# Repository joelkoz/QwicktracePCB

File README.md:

# Qwicktrace Pro PCB
Qwicktrace PCB is the software component of the QwickFab PCB open source desktop circuit board fabrication system.
The system dramatically reduces the time and skill required to make top quality single and double sided circuit 
boards for prototyping and one off use. Using QwickFab PCB, making a PCB is as simple as uploading your Gerber files to 
the Pro controller, selecting the process you wish to use to create the board, and then following the on-screen step
by step instructions. 

# Overview
The QwickFab desktop fabrication system consists of three major hardware components and one optional one:

1. The Qwicktrace Pro Controller is small control device with touchscreen and joystick powered by a Raspberry Pi 4 and the software
found in this repository. It is comprised of a software stack and UI for controlling the other two hardware components below. The 
Controller can run either of the two other components individually, or together as a complete desktop PCB fabrication system.

2. The Qwicktrace Exposure Table is a small device for quickly exposing photosensitive copper boards to ultraviolet light masked using a process called "Masked Stereolithography" (MSLA). The all new design of this exposure system adds an amber LED "safe light" for illuminating the mask for end user board positioning that is invisible to the photosenstive board.

3. The Qwickmill mini CNC is a small desktop CNC machine designed specifically for working with small printed circuit boards. It can
quickly drill the holes needed by through hole components on boards processed with the Exposure table.  It can also mill an entire PCB on blank copper boards using special ingraving bits. This is handy if your board is simple enough as to not need the better resolution of the exposure table, or if you are on a budget and would prefer not to spend the extra money on photosensitive boards. 
Finally, the Qwickmill can be used to cut board stock down to smaller sizes.

4. The QwickEtch Etching tank is a small container that can be used to quickly etch boards exposed with the Exposure table using
a minimal mount of equipment. While any type of container can be used, the QwickEtch tank has an air pump powered agitator in
in, removing the need for you to manually rock the etching tank.

The software on the Pro Controller (source code found on this repo) handles the more challenging aspects of making a PCB, such as aligning the drilling with the traces made on the exposure table, or positioning the opposite side of a board on a double sided PCB.

While the above hardware components make for a convenient set of tools, many Makers already have existing equipment they'd like
to use in place of a QwickFab component. You are free to mix and match any or all of the components that you wish.  You could
in theory build NONE of the hardware components and simply run the Qwicktrace software on an old laptop or pre-existing 
Raspberry Pi build.  The Qwickmill is built upon the open source standard Grbl controller. If you already own a CNC machines that uses Grbl, you can use that instead. It is easy to create a cable that connects from the Pro Controller to any CNC machine, such a 3018 or 1610. If you are on a budget, you can sometimes source a kit for one of these machines for less money than the individual parts for building the Qwickmill.

# Software features

* Creates PCB trace masks directly from Gerber files in SVG for MSLA exposure and/or in g-code for isolation milling
* Software deskewing of traces and drill holes makes combining MSLA, milling, and/or double sided boards quick and easy.
* Software autoleveling ensures isolation milling traces are cut to perfect depth
* Drill/mill features works with any Grbl compatible CNC controller
* UI designed for small 3.5" touchscreen
* Supports joystick input via ADS1115 for easy jogging of CNC machine and alignment of drill holes
* Turns Raspberry Pi into a remote access server and controller for Grbl CNC machines

# DIY construction of a QwickFab system

The Qwickfab Pro system is made from parts printed with your 3D printer as well as easy to obtain off the shelf parts. The
STL files for this project can be found here in this repo in the `hardware/*/stl` directories. A complete bill of materials can be
found in the `docs` directory.

Build instructions with project discussion is located on the project's [Hackaday Project Page](https://hackaday.io/project/182645-qwickfab-pcb)

To install the software on the Raspberry Pi, see the file `Setting up Raspberry Pi`, also in `docs`

# Development

The Qwicktrace user interface on the Pro Controller is a touchscreen app written in NodeJS/Javascript and built with the
Electron framework.  This UI is layered on top of a software stack comprised of many great open source software packages. These include:

1. [Tracespace](https://github.com/tracespace) Gerber processing library for Javascript
2. [pcb2gcode](https://github.com/pcb2gcode/pcb2gcode) Gerber to GCode utility for milling isolation traces
3. [CNCjs](https://github.com/cncjs/cncjs) Web interface and Grbl server for CNC machine control
4. [EventEmitter2](https://github.com/EventEmitter2/EventEmitter2) Advanced event handling for NodeJS

For additional technical information on the Qwicktrace software architecture, see the `docs` directory

---
### Do you find my work useful?

---

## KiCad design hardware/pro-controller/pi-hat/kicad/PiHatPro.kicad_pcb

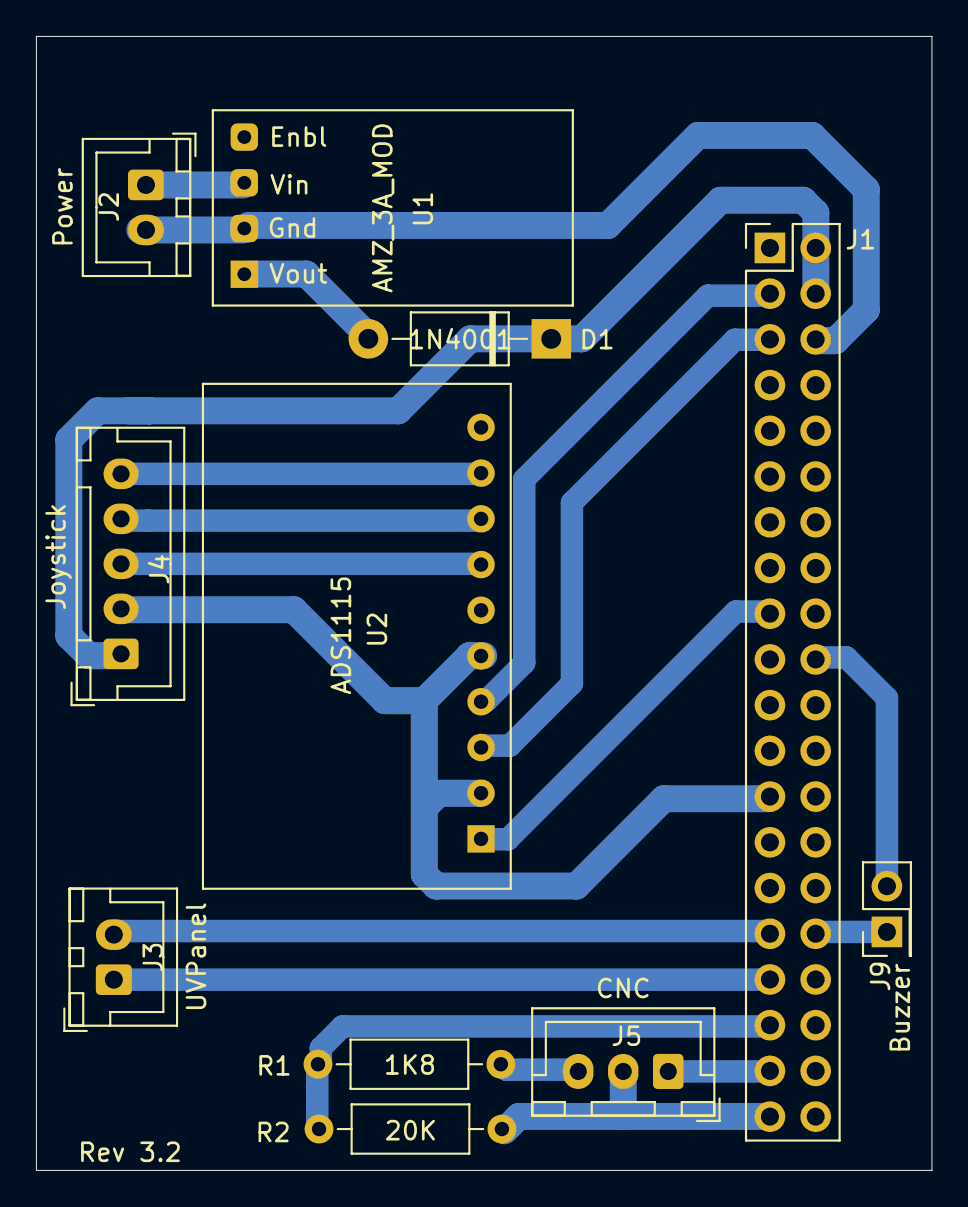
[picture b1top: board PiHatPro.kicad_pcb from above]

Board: 4 copper layers, 49.8 x 63.0 mm, 11 parts (0 on the bottom side), 16 nets.

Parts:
D1: 1N4001; D_DO-41_SOD81_P10.16mm_Horizontal
J1: Raspberry_Pi_2_3; PinSocket_2x20_P2.54mm_BacksideMount
J2: Power; JST_XH_B2B-XH-A_1x02_P2.50mm_Vertical
J3: UVPanel; JST_XH_B2B-XH-A_1x02_P2.50mm_Vertical
J4: Joystick; JST_XH_B5B-XH-A_1x05_P2.50mm_Vertical
J5: CNC; JST_XH_B3B-XH-A_1x03_P2.50mm_Vertical
J9: Buzzer; PinHeader_2x01_P2.54mm_Vertical
R1: 1K8; R_Axial_DIN0207_L6.3mm_D2.5mm_P10.16mm_Horizontal
R2: 20K; R_Axial_DIN0207_L6.3mm_D2.5mm_P10.16mm_Horizontal
U1: AMZ_3A_MOD; Amazon_3A_Power_Module
U2: ADS1115; Adafruit_ADS1115_Module

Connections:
+3V3: J1.1, J1.17, U2.1
+5V: D1.1, J1.2, J1.4, J4.1
+24V: J2.1, U1.3
Buzzer: J1.32, J9.1
GND: J1.6, J1.9, J1.14, J1.20, J1.25, J1.30, J1.34, J1.39, J2.2, J4.2, J5.2, J9.2, R2.2, U1.2, U2.2, U2.5
JOYSTICK_SW: J4.5, U2.9
JOYSTICK_X: J4.3, U2.7
JOYSTICK_Y: J4.4, U2.8
LaserControl: J1.37, J5.1
unnamed: D1.2, U1.1
SCL: J1.5, U2.3
SDA: J1.3, U2.4
UVExpose: J1.31, J3.2
UVSafe: J1.33, J3.1
ZProbe3V3: J1.35, R1.2, R2.1
ZProbeIn: J5.3, R1.1

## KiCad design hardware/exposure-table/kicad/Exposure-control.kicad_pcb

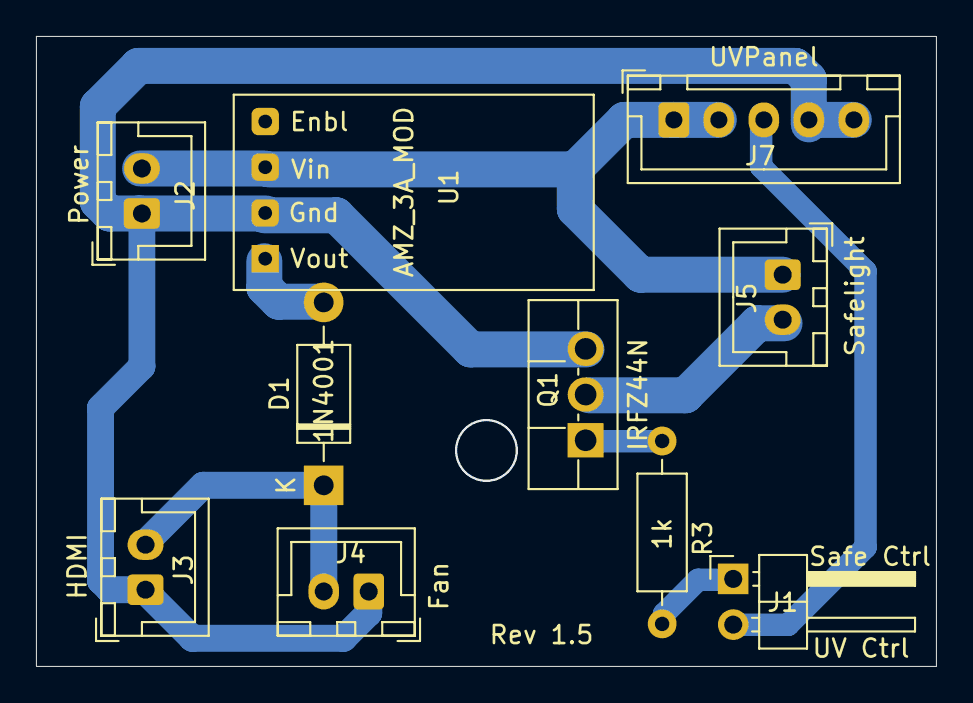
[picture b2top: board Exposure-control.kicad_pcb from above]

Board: 2 copper layers, 50.0 x 35.0 mm, 10 parts (0 on the bottom side), 8 nets.

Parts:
D1: 1N4001; D_DO-41_SOD81_P10.16mm_Horizontal
J1: Light Control; PinHeader_1x02_P2.54mm_Horizontal
J2: Power; JST_XH_B2B-XH-A_1x02_P2.50mm_Vertical
J3: HDMI; JST_XH_B2B-XH-A_1x02_P2.50mm_Vertical
J4: Fan; JST_XH_B2B-XH-A_1x02_P2.50mm_Vertical
J5: Safelight; JST_XH_B2B-XH-A_1x02_P2.50mm_Vertical
J7: UVPanel; JST_XH_B5B-XH-A_1x05_P2.50mm_Vertical
Q1: IRFZ44N; TO-220F-3_Vertical
R3: 1k; R_Axial_DIN0207_L6.3mm_D2.5mm_P10.16mm_Horizontal
U1: AMZ_3A_MOD; Amazon_3A_Power_Module

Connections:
+5V: D1.1, J3.2, J4.2
+24V: J2.2, J5.1, J7.1, J7.2, U1.3
GND: J2.1, J3.1, J4.1, J7.4, J7.5, Q1.3, U1.2
unnamed: D1.2, U1.1
unnamed: Q1.1, R3.2
SafelightControl: J1.1, R3.1
SafelightGnd: J5.2, Q1.2
UVControl: J1.2, J7.3

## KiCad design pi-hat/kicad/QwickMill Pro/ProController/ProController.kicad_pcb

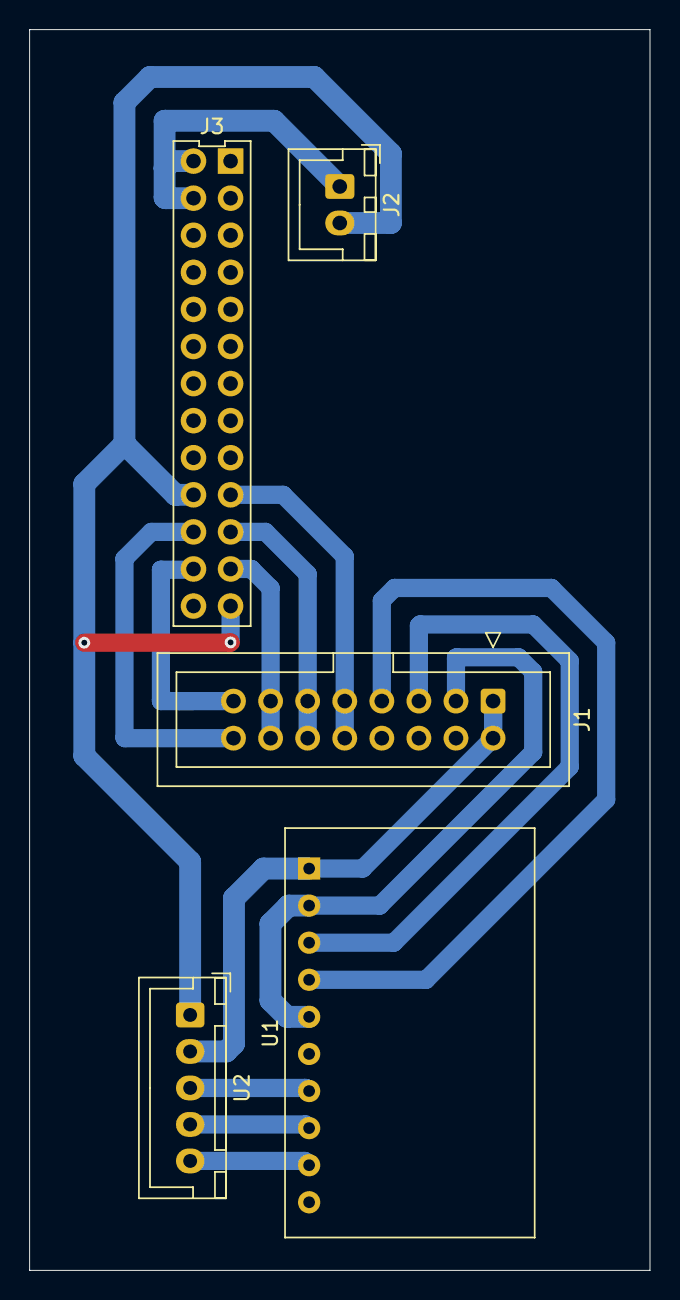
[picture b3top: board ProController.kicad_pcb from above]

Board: 2 copper layers, 42.5 x 85.0 mm, 5 parts (0 on the bottom side), 13 nets.

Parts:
J1: IDC16; IDC-Header_2x08_P2.54mm_Vertical
J2: Pro Power; JST_XH_B2B-XH-A_1x02_P2.50mm_Vertical
J3: HDMI-LCD; Pi_Header_Pins_Backside_Mount_26
U1: ADS1115; Adafruit_ADS1115_Module
U2: JOYSTICK; JST_XH_B5B-XH-A_1x05_P2.50mm_Vertical

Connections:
+3V3: J1.1, J1.2, U1.1, U2.2
+5V: J2.1, J3.2, J3.4
GND: J1.3, J2.2, J3.20, J3.25, U1.2, U1.5, U2.1
MISO: J1.11, J1.12, J3.21
MOSI: J1.9, J1.10, J3.19
SCL: J1.5, U1.3
SDA: J1.7, U1.4
SLCK: J1.13, J1.14, J3.23
SW: U1.9, U2.5
T_CS: J1.15, J3.24
T_IRQ: J1.16, J3.22
VRX: U1.7, U2.3
VRY: U1.8, U2.4

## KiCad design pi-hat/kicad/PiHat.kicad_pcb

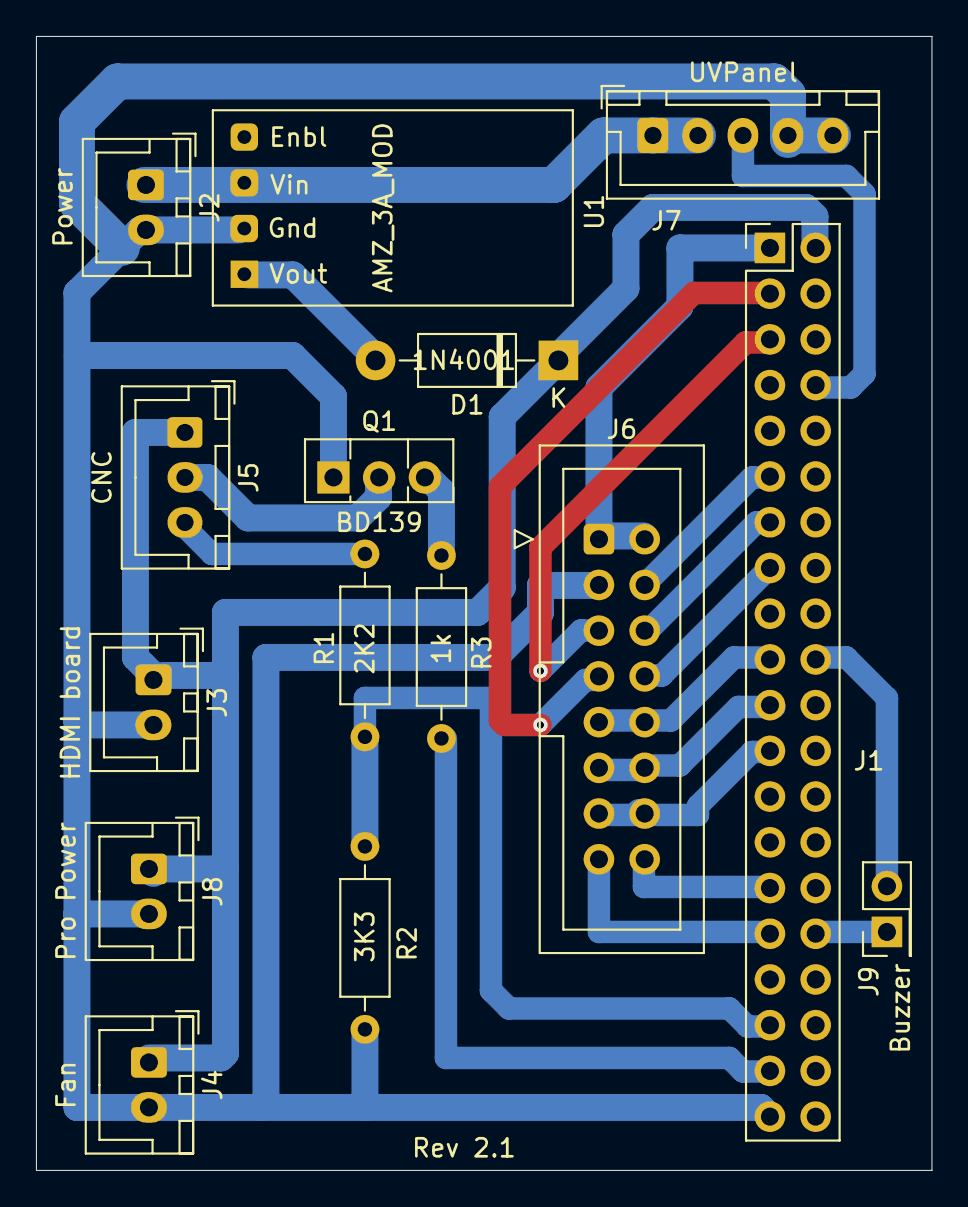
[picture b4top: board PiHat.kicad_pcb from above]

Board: 2 copper layers, 49.8 x 63.0 mm, 15 parts (0 on the bottom side), 22 nets.

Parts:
D1: 1N4001; D_DO-41_SOD81_P10.16mm_Horizontal
J1: Raspberry_Pi_2_3; PinSocket_2x20_P2.54mm_BacksideMount
J2: Power; JST_XH_B2B-XH-A_1x02_P2.50mm_Vertical
J3: HDMI board; JST_XH_B2B-XH-A_1x02_P2.50mm_Vertical
J4: Fan; JST_XH_B2B-XH-A_1x02_P2.50mm_Vertical
J5: CNC; JST_XH_B3B-XH-A_1x03_P2.50mm_Vertical
J6: IDC16; IDC-Header_2x08_P2.54mm_Vertical
J7: UVPanel; JST_XH_B5B-XH-A_1x05_P2.50mm_Vertical
J8: Pro Power; JST_XH_B2B-XH-A_1x02_P2.50mm_Vertical
J9: Buzzer; PinHeader_2x01_P2.54mm_Vertical
Q1: BD139; TO-126-3_Vertical
R1: 2K2; R_Axial_DIN0207_L6.3mm_D2.5mm_P10.16mm_Horizontal
R2: 3K3; R_Axial_DIN0207_L6.3mm_D2.5mm_P10.16mm_Horizontal
R3: 1k; R_Axial_DIN0207_L6.3mm_D2.5mm_P10.16mm_Horizontal
U1: AMZ_3A_MOD; Amazon_3A_Power_Module

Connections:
+3V3: J1.1, J6.1, J6.2
+5V: D1.1, J1.2, J3.1, J4.1, J5.1, J8.1
+24V: J2.1, J7.1, J7.2, U1.3
Buzzer: J1.32, J9.1
CS: J1.11, J6.4
DC: J1.13, J6.6
GND: J1.20, J1.39, J2.2, J3.2, J4.2, J6.3, J7.4, J7.5, J8.2, J9.2, Q1.1, R2.2, U1.2
LaserControl: J1.37, R3.1
LaserGnd: J5.2, Q1.2
MISO: J1.21, J6.11, J6.12
MOSI: J1.19, J6.9, J6.10
unnamed: D1.2, U1.1
unnamed: Q1.3, R3.2
RESET: J1.15, J6.8
SCL: J1.5, J6.5
SDA: J1.3, J6.7
SLCK: J1.23, J6.13, J6.14
T_CS: J1.31, J6.15
T_IRQ: J1.29, J6.16
UVControl: J1.8, J7.3
ZProbe3V3: J1.35, R1.2, R2.1
ZProbeIn: J5.3, R1.1

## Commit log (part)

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2021-03-26 Update LICENSE
2021-03-26 Added TFT wiring table. Print to PDF
    Updated Numbers spreadsheet. Printed to PDF for non Mac users.
2021-03-27 Create autostart-app
    Add LXDE autostart-app file to pi-config directory
2021-03-27 Update README.md
    Small corrections.
2021-03-29 Delete PiHat.drl.nc
    GCODE drill file was misplaced
2021-03-29 Script to bundle files for easypcbusa.com
    Script creates a .zip file compatible with EasyPCBUSA.com for PCB fab
2021-03-30 Updated pin numbering spreadsheet
2021-04-05 Catch errors in user file formats
2021-04-05 Fix run command
2021-05-20 Use Sparkmaker UV lamp on pin 14
    Move UV exposure control to pin 14. Pin 26 is now target (laser) pointer on/off for optional CNC machine.
2021-05-20 Added PCB for optional "Pro Controller"
    Pro Controller can work with QwickMill PCB CNC machine
2021-05-20 Update PiHat-B_Cu.gbr
    Rev 2 of PiHat
2021-05-23 UV lamp on Rev 2 is on pin 14
2021-05-26 Save calibration data from joystick test
2021-05-28 WIP: CNC code
2021-05-28 Added ability to jog Z axis
2021-06-01 Updated PiHat schematic to reflect proper values to read z-probe
2021-06-01 Ability to control laser pointer brightness
2021-06-02 Update laser pointer offsets
2021-06-09 RasPi version of pcb2gcode v2.4
2021-06-21 config.json globally available
    The contents of config.json is available app, render, and javascript side via 'appConfig' variable
2021-06-22 Selection list now has optional list filter function
2021-06-22 Initial code for hole drilling support
2021-06-22 Latest config used for dev on my Mac
2021-06-24 Drill alignment page uses transforms
    Use canvas transformation matrix to orient and scale hole positions
2021-06-24 Use mouse only when debugging
    Allow mouse clicks only when debugging alignment
2021-06-25 Updated default configuration files
    Created additional default configurations, and removed config.json from repo
2021-06-26 WIP: Deskew and drill board using CNC
    Fixes and additions to cnc drilling code. Use transformation matrix to convert to/from pcb coordinates and mill coordinates.
2021-06-27 Corrected pin definitions in standard Pi-Hat
2021-06-28 Use fs-extra
    Use fs-extra for certain file handling processes
2021-06-30 Rename LEDController to UVController
    Rename to UVController to clarify its purpose
2021-07-11 Added getSize method to PCBProject
    PCBProject will read size data from existing gerber files if not job file is present
2021-07-11 Refactor to project based profiles
    The file loader system is now project based vs. individual file based. Rather than requesting an individual gerber file to be loaded and a profile that specifies how to expose that gerber file, the f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
    Mixed in with this refa
2021-07-11 Remove unused method in UIController
2021-07-11 Remove old cancelProcesses() implementation
    UIController had old implementation of cancelProcesses() hanging around
2021-07-16 Correct joystick jog direction
2021-07-16 Fixes to wizard subsystem
    Wizard buttons had wrong css class. cancelWizard() now fault tolerant
2021-07-16 Fix display of conditional buttons
    Certain buttons are available if certain conditions are met. This fixes the code that makes that happen
2021-07-17 Move promise utility functions to common package
    Create a package in common dir for promise utility functions
2021-07-17 Add "Reset mill" option to settings
2021-07-17 Fixes to CNCController
    Debounce joystick button, popup messages on error events, initCNC() should reset sender and feeder also, add a timeout to waitForState()
2021-07-18 Fixes to mill setup
    Use proper coordinate system when commanding machine during setup.
2021-07-18 Updates to default config files
    Update config example files based on latest testing
2021-07-19 Display probe status during autolevel
2021-07-19 Ignore SVG files created by pcb2gcode
2021-07-20 zProbe process re-written as async methods
    Converted promise code in CNCController to use async/await instead.
2021-07-21 Add margin parameter to GerberUtils rotate
    Initial code to fix rotation adjustments when edge cuts are unknown.
2021-07-22 Improved async probing code
    More testing and tweaks to z probe async code
2021-07-22 Improved code docs
    Added some comments and changed some variable names
2021-07-25 Fixed missing property reference
    GerberData refactor changed definition of boundingBox property
2021-07-25 Remove unused require
2021-07-26 Warnings for unrecognized gerber file names
    Added console warnings to PCBProject to show when gerber files could not be recongized by gerber libraries
2021-07-26 Fixed Z search speed on PCB z probe
2021-07-27 increase trace milling depth
2021-07-27 First feature complete version of milling
2021-09-06 Option to start a wizard on an arbitrary page
    Added option to UIController.startWizard() to allow wizard to be started on a page other than step #1.
2021-09-06 Initial universal event messaging code
    Initial version of code that will allow a single method of sending event messaging. MainMQ on main process side, and new RenderMQ on render side now use EventEmitter2 library, which adds ability to d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
2021-09-07 New RPC mechanism (with ZProbe settings)
    Added new RPC mechanism and refactored the SettingsController to use it. As demonstration of usage, z probing the pad was added as an option to the Settings UI.
2021-09-07 Remove pcbFrame references
    The PCB frame is no longer used in the design
2021-09-08 Improved error messages when untilXX() promises are rejected.
2021-09-08 Refactor mill process (forgot to check in this file)
2021-09-08 Refactored remaining class interactions to new RPC mechanism
    All remote procedure calls now use the new RPC mechanism (including older code classes).
2021-09-11 Corrected stock handling code
    Can now properly detect if currently loaded and processed stock can be used in the next operation
2021-09-11 Report jog mode as event. Add setPointer to API()
2021-09-14 Improved jogging control via joystick
2021-09-17 Option to specify feed rate for goto()
2021-09-18 Only zprobe once per board when milling
2021-09-18 Update millproject
    The mill project settings used for first successful PCB mill
2021-09-27 Improved Jog code
    Improved code for jogging CNC. Fixed "jog stop" command.
2021-09-28 New settings: Calibrate laser pointer and test limit switches
    Added laser pointer calibration and limit and probe switch testing to settings. These are initial use cases of expanded functionality added to CNCController (setting RPM via API, getting pin status r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
2021-09-30 Display stack trace if CNC times out waiting on events
2021-09-30 Config setAndSave() callable from render process
    Added method setAndSave() to set a specific configuration value and immediately save the results. Method is available as remote procedure call from render process
2021-10-08 Initial files for splash screen
2021-10-08 Latest config.txt for Pro controller using UCTRONICS UC640
2021-10-14 Added Safelight control to UVController
2021-10-23 Added "Vertical Cut PCB" feature
    Can now do a vertical cut on the PCB to make two separate pieces
2021-10-23 Create laser-control-test.js
    Code to test the laser light connection
2021-10-23 Removed temp files from test dir
2021-10-23 Reorganize PCB design directories
    Re-arrange PCB design files
2021-10-23 Updated config files
2021-10-23 Initial code to drill following mill
2021-10-25 Update profile-example-drill.txt
    Save copy of latest drill profile
2021-10-25 Update millproject
    Tweaked values based on testing
2021-10-25 Do not use joystick button to select drill positions
2021-10-25 Joystick i2c fault tolerance
    Ignore transient errors on ADS1115 joystick interface
2021-10-25 Remove half bit adjustments for cuts
2021-10-25 FIX: Incorrect ZHeight at beginning of milling
2021-10-26 Fix: drilling after milling needs actual stock used in profile
    Drill holes were off immediately following mill due to "actual" property from last profile not in new profile stock property.
2021-10-26 Fixed milling progress display
2021-10-28 Exposure control board rev 1.5
    Moved signal connectors to opposite side. Added screw hole to connect to exposure table body
2021-10-28 Added "Goto" button in VCut feature
    VCut can now go to user specified location vs. using joystick.
2021-10-29 Fixed touchscreen inputs
    Added X libinput config file for UC640 touchscreen
2021-10-29 Create cnc-init.json
    List of machine configuration options
2021-10-31 Refactor Joystick handling
    Created new JoystickController class that allows the joystick to be used independently of the cnc machine.
2021-11-02 Remove unused files
2021-11-03 Modify board profiles
2021-11-03 Exposure mask calibration. Utility menu with option filtering
2021-11-05 Cursor changed from crosshairs to inverted box (i.e. the "Cursor box")
2021-11-06 Refactor joystick input on ExposureCanvas to work with direction/speed
2021-11-06 Joystick sample interval option added to config file
2021-11-06 Accurate mask area offsets as found by keypad entry
2021-11-09 Add optional i2c property to Joystick config
2021-11-10 Added code to make spoil board using mill
2021-11-10 FIX: Vertical cut on spoil board alignment channels were off
2021-11-10 Updated default config files for new config driven css
2021-11-10 Added "Horizontal cut" to milling services
2021-11-11 Fixes to exposure mask display and calibration
2021-11-12 New project README.md
    New readme describing the entire Qwickfab system
2021-11-13 Initial etch tank STL and instructions
2021-11-16 Added STL file for etch tank
2021-11-16 Disable bluetooth in config
2021-11-16 Added "Software features" list to README
2021-11-16 Added images to README
    Added pictures of the system to the README file
2021-11-16 Update README.md
    Fix typo
2021-11-17 Added sample screen shots
    Created dir docs/images for sample screen shots
2021-11-17 Create Bill of Materials.txt
    Initial bill of materials list
2021-12-15 Added schematics for ProController wiring
2021-12-15 Move STL files to hardware directory
2021-12-17 Pi Hat is now single sided
    Pi Hat Rev 3.1 is now completely single sided for easier DIY fabrication
2022-01-03 Update README.md
    Reference project's Hackaday page
2022-01-03 Fixes to PiHatPro pcb board
2022-01-03 gitignore pcb bundle .zip files
2022-01-04 Use cursor box for stock sizing of exposure area
2022-01-05 Add explicit "no change" button to board positioning
2022-01-05 Fixes for double sided exposures
    Fixes for testing of double sided exposures
2022-01-05 Added profiles for two sided exposure boards
2022-01-06 Use actual stock dimensions if present
2022-01-06 Fix alignment issue bottom board
    trace position for bottom side needs to be corrected if stock height does not match original board height and vertical position is not being altered via "GerberTransform.positionCopper()"
2022-01-06 Tweaked copper positioning margins
2022-02-25 Fix rotated copper positions in GerberTransforms
    Rotating copper the moving right had wrong positioning
2022-02-25 FIX: Exposing needs to mirror bottom also
    Bottom side is mirrored if milling or exposing
2022-06-08 Use Grbl "pin report" vs. zprobe hardware splice
    ZProbe state detection can be done via Grbl's "pin report" feature, vs. having to splice directly into the zprobe signal line and re-direct to a RazPi GPIO port.
2022-06-08 Skip zpad calculations when probing for pcb surface
    ZPad no longer used for pcb surface probe
2022-06-08 Update config-3018.json
    Latest config used by 3018 testing
2025-04-11 Update millproject-3018
    Tweaked settings for 3018 milling
